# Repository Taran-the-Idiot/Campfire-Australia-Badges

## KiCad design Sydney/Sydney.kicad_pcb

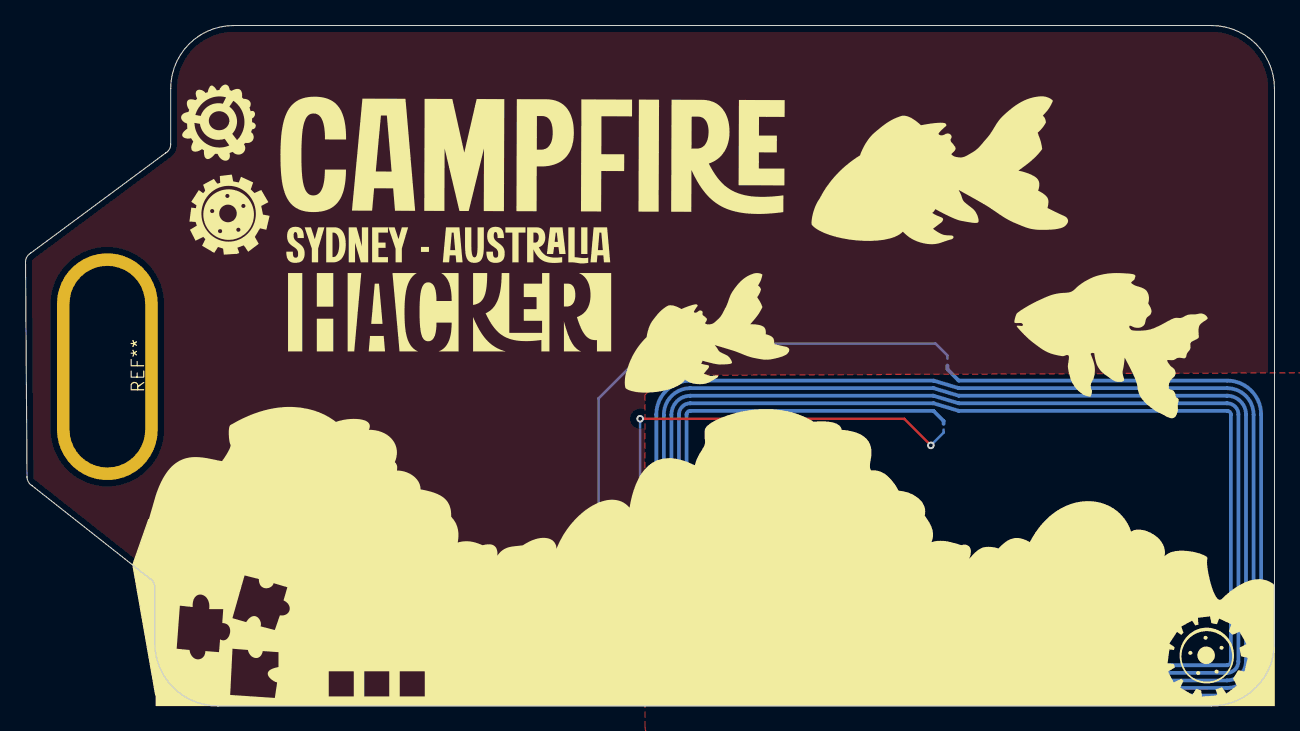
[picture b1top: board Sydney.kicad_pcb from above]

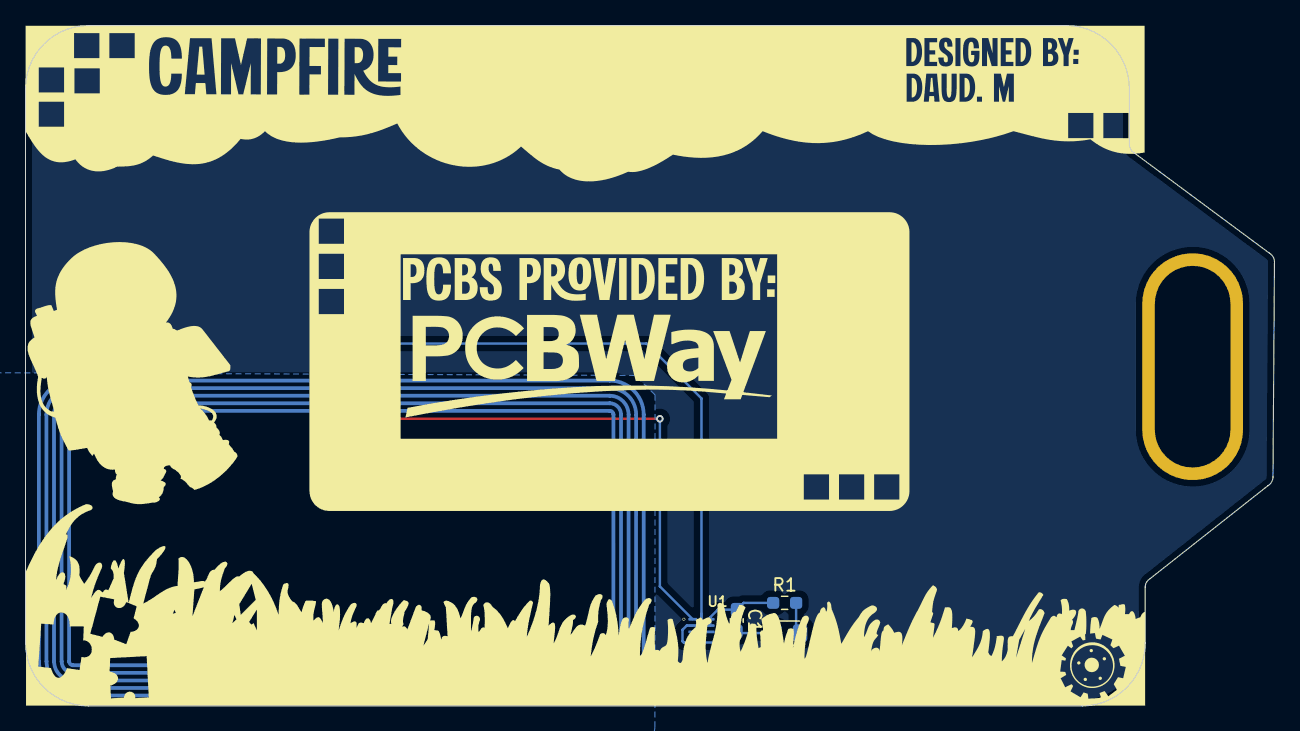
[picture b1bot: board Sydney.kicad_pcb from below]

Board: 2 copper layers, 99.1 x 54.0 mm, 5 parts (5 on the bottom side), 5 nets.

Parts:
C1: C; C_0603_1608Metric_Pad1.08x0.95mm_HandSolder
D1: LED; LED_0805_2012Metric_Pad1.15x1.40mm_HandSolder
J1: Conn_01x02_Pin; 25x_48mm NFC Antenna
R1: R; R_0603_1608Metric_Pad0.98x0.95mm_HandSolder
U1: NT3H2111W0FHKH; QFN8P50_160X160X50L40X20N

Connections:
unnamed: D1.2 (A), R1.2
unnamed: C1.2, D1.1 (K), U1.2 (VSS)
unnamed: J1.1, U1.8 (LB)
unnamed: J1.2, U1.1 (LA)
unnamed: C1.1, R1.1, U1.6 (VCC), U1.7 (VOUT)

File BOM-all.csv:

Designator,Quantity,Value,Footprint,Package,MPN,DNP,Mount_Type,Description,Sim.Pins,MANUFACTURER
C1,1,C,C_0603_1608Metric_Pad1.08x0.95mm_HandSolder,0603,,,smt,220nF 25V X7R ±10% 0603 Multilayer Ceramic Capacitors MLCC - SMD/SMT ROHS,,any/open
D1,1,LED,LED_0805_2012Metric_Pad1.15x1.40mm_HandSolder,0805,,,smt,-40℃~+85℃ 1.8V~2.4V 120° 175mcd 40mW 584nm~594nm 596nm Discrete Diode Water Clear Yellow 0805 LED Indication - Discrete ROHS,1=K 2=A,any/open
U1,1,NT3H2111W0FHKH,QFN8P50_160X160X50L40X20N,XQFN-8,,,smt,"106Kbit/s 13.56MHz 3.3V I2C ISO 14443A,NFC XQFN-8(1.6x1.6) RFID ICs ROHS",,NXP Semiconductors
R1,1,R,R_0603_1608Metric_Pad0.98x0.95mm_HandSolder,0603,,,smt,-55℃~+155℃ 100mW 47Ω 75V Thick Film Resistor ±1% ±100ppm/℃ 0603 Chip Resistor - Surface Mount ROHS,,any/open

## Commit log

2026-01-07 init
2026-01-07 commit stuff
2026-01-20 lots of stuff
2026-01-20 i hate kicad and figma
2026-01-20 me want to die
2026-01-20 finally works ish
2026-01-20 bleh
2026-01-20 copy pasting to other cities
2026-01-20 bonk
2026-01-20 kablewey
2026-01-22 STINKY
2026-01-22 AGHGDGZFDFHGJHGFH
2026-01-22 [INSERT KEYBOARD SLAM HERE]
2026-01-22 [INSERT SECOND KEYBOARD SLAM HERE]
2026-01-22 POTATO
2026-01-22 testing stuff
2026-01-22 ALL THE ASSETS LEFT. NOW ONLY PCB SHIT TO GO
2026-01-22 GTTRHIUIUHRREHIGMOEGRXNUWE
2026-01-22 PCBS DONE BUT IM NOT FREE
2026-01-22 BOM DONE
2026-01-22 NJKDHFJKWHFEHEWK
2026-01-22 IM FREEEEEEEE
2026-01-30 flfjkjdfsafjahgjf
